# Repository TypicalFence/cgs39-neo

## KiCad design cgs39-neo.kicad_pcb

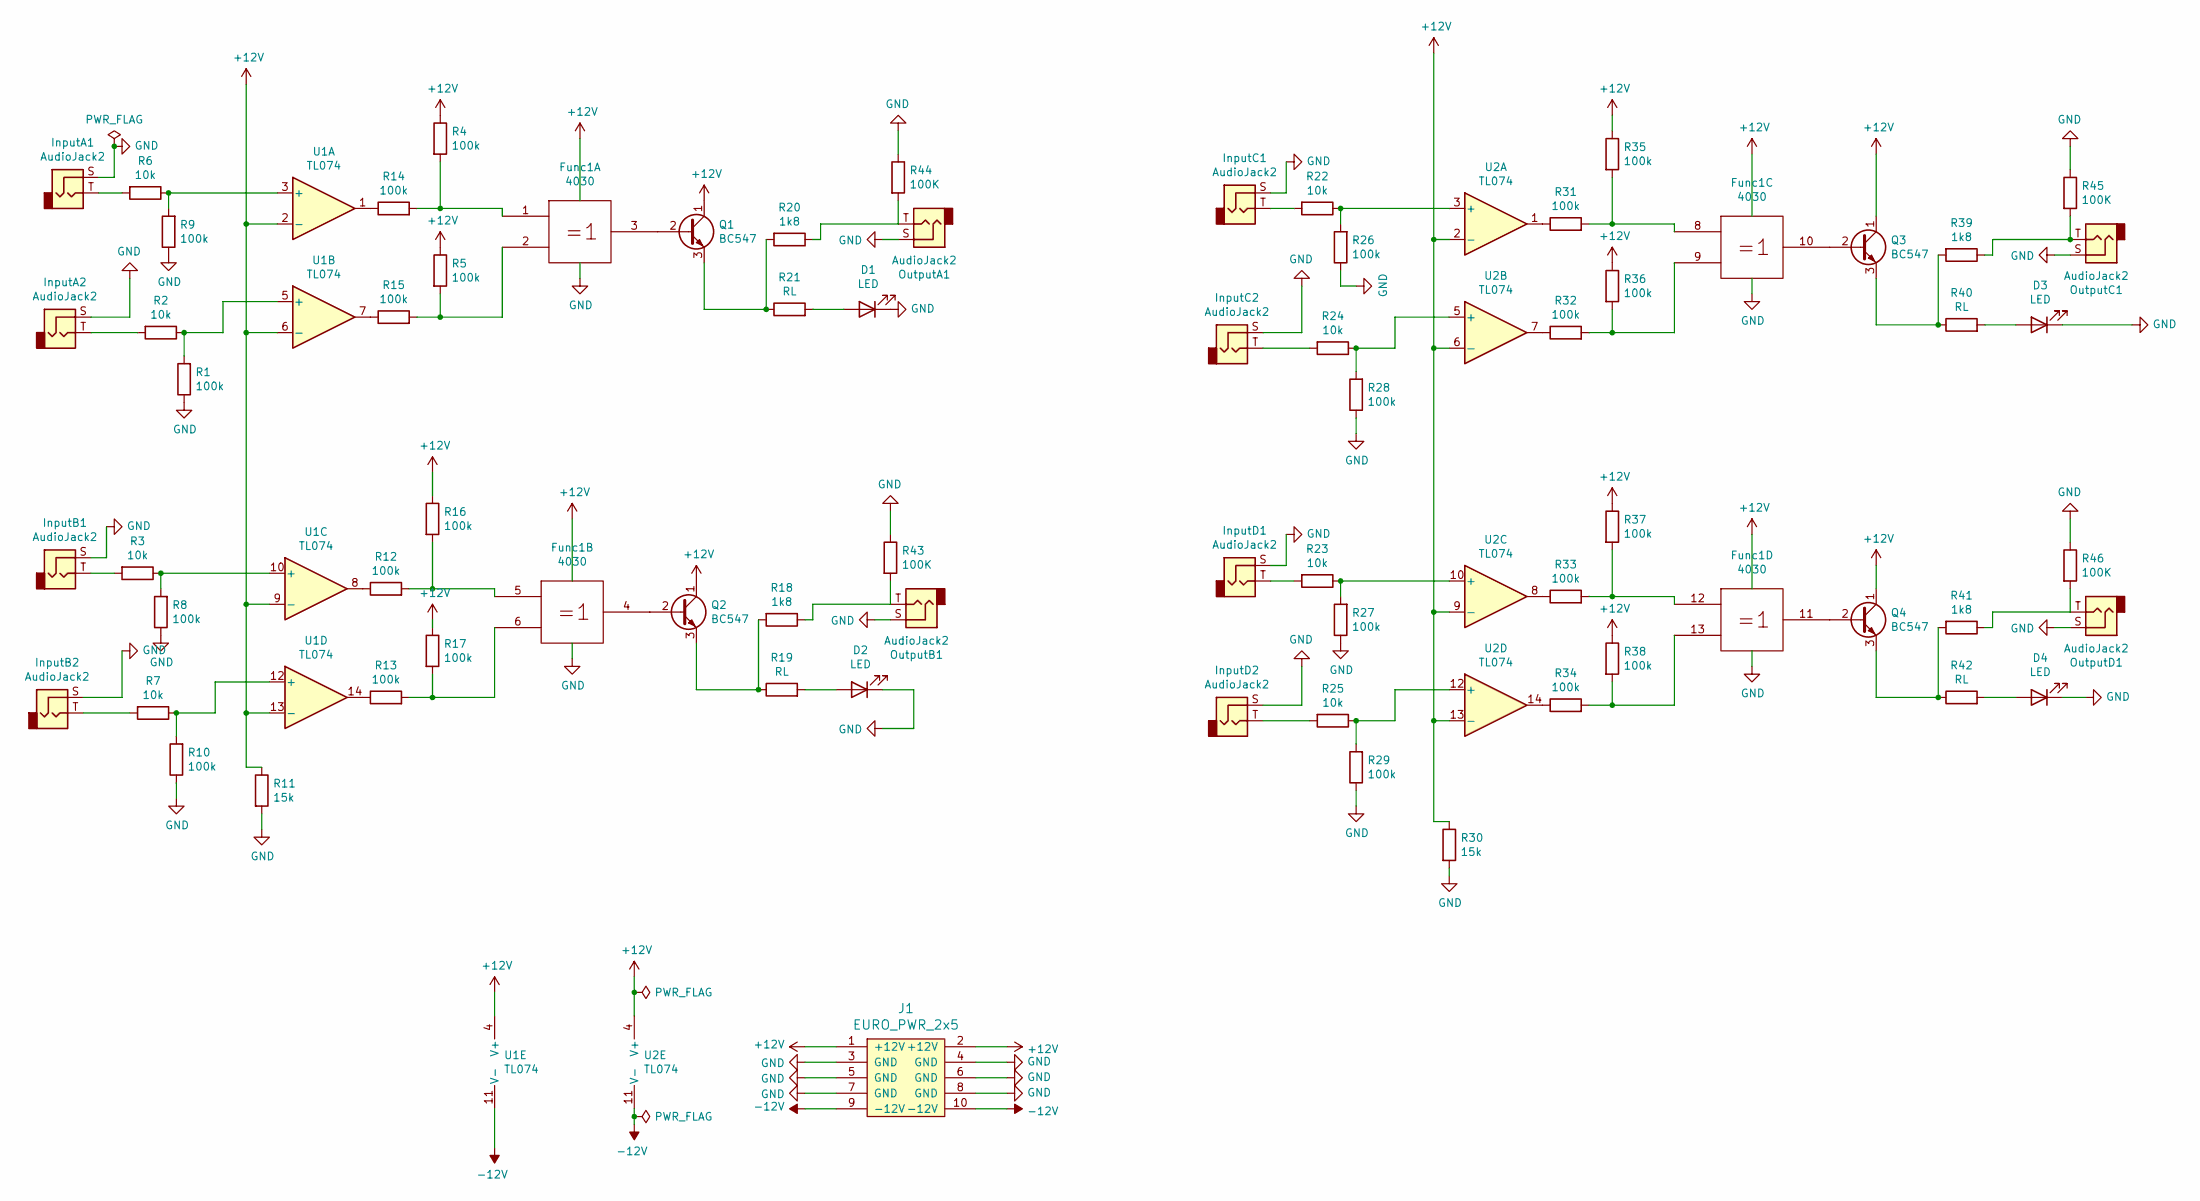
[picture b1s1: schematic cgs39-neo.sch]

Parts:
D1, D2, D3, D4: LED; LED_D5.0mm
Func1: 4030; DIP-14_W7.62mm
InputA1, InputA2: AudioJack2; SIMPLE-JACK-2PIN-THT
InputB1, InputB2: AudioJack2; SIMPLE-JACK-2PIN-THT
InputC1, InputC2: AudioJack2; SIMPLE-JACK-2PIN-THT
InputD1, InputD2: AudioJack2; SIMPLE-JACK-2PIN-THT
J1: EURO_PWR_2x5; PinHeader_2x05_P2.54mm_Vertical
OutputA1: AudioJack2; SIMPLE-JACK-2PIN-THT
OutputB1: AudioJack2; SIMPLE-JACK-2PIN-THT
OutputC1: AudioJack2; SIMPLE-JACK-2PIN-THT
OutputD1: AudioJack2; SIMPLE-JACK-2PIN-THT
Q1, Q2, Q3, Q4: BC547; TO-92_Inline
R1, R4, R5, R8, R9, R10, R12, R13, R14, R15, R16, R17, R26, R27, R28, R29, R31, R32, R33, R34, R35, R36, R37, R38: 100k; R_Axial_DIN0204_L3.6mm_D1.6mm_P5.08mm_Horizontal
R2, R3, R6, R7, R22, R23, R24, R25: 10k; R_Axial_DIN0204_L3.6mm_D1.6mm_P5.08mm_Horizontal
R11, R30: 15k; R_Axial_DIN0204_L3.6mm_D1.6mm_P5.08mm_Horizontal
R18, R20, R39, R41: 1k8; R_Axial_DIN0204_L3.6mm_D1.6mm_P5.08mm_Horizontal
R19, R21, R40, R42: RL; R_Axial_DIN0204_L3.6mm_D1.6mm_P5.08mm_Horizontal
R43, R44, R45, R46: 100K; R_Axial_DIN0204_L3.6mm_D1.6mm_P5.08mm_Horizontal
U1, U2: TL074; DIP-14_W7.62mm

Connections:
+12V: Func1.14 (Vdd), J1.1 (+12V), J1.2 (+12V), Q1.1 (C), Q2.1 (C), Q3.1 (C), Q4.1 (C), R4.1, R5.1, R11.1, R16.1, R17.1, R30.1, R35.1, R36.1, R37.1, R38.1, U1.2 (-), U1.4 (V+), U1.6 (-), U1.9 (-), U1.13 (-), U2.2 (-), U2.4 (V+), U2.6 (-), U2.9 (-), U2.13 (-)
-12V: J1.9 (-12V), J1.10 (-12V), U1.11 (V-), U2.11 (V-)
GND: D1.1 (K), D2.1 (K), D3.1 (K), D4.1 (K), Func1.7 (Vss), InputA1.S, InputA2.S, InputB1.S, InputB2.S, InputC1.S, InputC2.S, InputD1.S, InputD2.S, J1.3 (GND), J1.4 (GND), J1.5 (GND), J1.6 (GND), J1.7 (GND), J1.8 (GND), OutputA1.S, OutputB1.S, OutputC1.S, OutputD1.S, R1.1, R8.1, R9.1, R10.1, R11.2, R26.1, R27.1, R28.1, R29.1, R30.2, R43.1, R44.1, R45.1, R46.1
unnamed: D1.2 (A), R21.2
unnamed: D2.2 (A), R19.2
unnamed: D3.2 (A), R40.2
unnamed: D4.2 (A), R42.2
unnamed: Func1.1, R4.2, R14.2
unnamed: Func1.2, R5.2, R15.2
unnamed: Func1.3, Q1.2 (B)
unnamed: Func1.4, Q2.2 (B)
unnamed: Func1.5, R12.2, R16.2
unnamed: Func1.6, R13.2, R17.2
unnamed: Func1.8, R31.2, R35.2
unnamed: Func1.9, R32.2, R36.2
unnamed: Func1.10, Q3.2 (B)
unnamed: Func1.11, Q4.2 (B)
unnamed: Func1.12, R33.2, R37.2
unnamed: Func1.13, R34.2, R38.2
unnamed: InputA1.T, R6.2
unnamed: InputA2.T, R2.2
unnamed: InputB1.T, R3.2
unnamed: InputB2.T, R7.2
unnamed: InputC1.T, R22.2
unnamed: InputC2.T, R24.2
unnamed: InputD1.T, R23.2
unnamed: InputD2.T, R25.2
unnamed: OutputA1.T, R20.1, R44.2
unnamed: OutputB1.T, R18.1, R43.2
unnamed: OutputC1.T, R39.1, R45.2
unnamed: OutputD1.T, R41.1, R46.2
unnamed: Q1.3 (E), R20.2, R21.1
unnamed: Q2.3 (E), R18.2, R19.1
unnamed: Q3.3 (E), R39.2, R40.1
unnamed: Q4.3 (E), R41.2, R42.1
unnamed: R1.2, R2.1, U1.5 (+)
unnamed: R3.1, R8.2, U1.10 (+)
unnamed: R6.1, R9.2, U1.3 (+)
unnamed: R7.1, R10.2, U1.12 (+)
unnamed: R12.1, U1.8
unnamed: R13.1, U1.14
unnamed: R14.1, U1.1
unnamed: R15.1, U1.7
unnamed: R22.1, R26.2, U2.3 (+)
unnamed: R23.1, R27.2, U2.10 (+)
unnamed: R24.1, R28.2, U2.5 (+)
unnamed: R25.1, R29.2, U2.12 (+)
unnamed: R31.1, U2.1
unnamed: R32.1, U2.7
unnamed: R33.1, U2.8
unnamed: R34.1, U2.14

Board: 2 copper layers, 70 parts (0 on the bottom side), 51 nets, no tracks yet.

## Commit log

2020-11-22 init
2020-11-22 add power & replace jacks
2020-11-22 resistor untangle
2020-11-23 i hate this
2020-11-24 trying to make smoll
2020-11-25 brogres
